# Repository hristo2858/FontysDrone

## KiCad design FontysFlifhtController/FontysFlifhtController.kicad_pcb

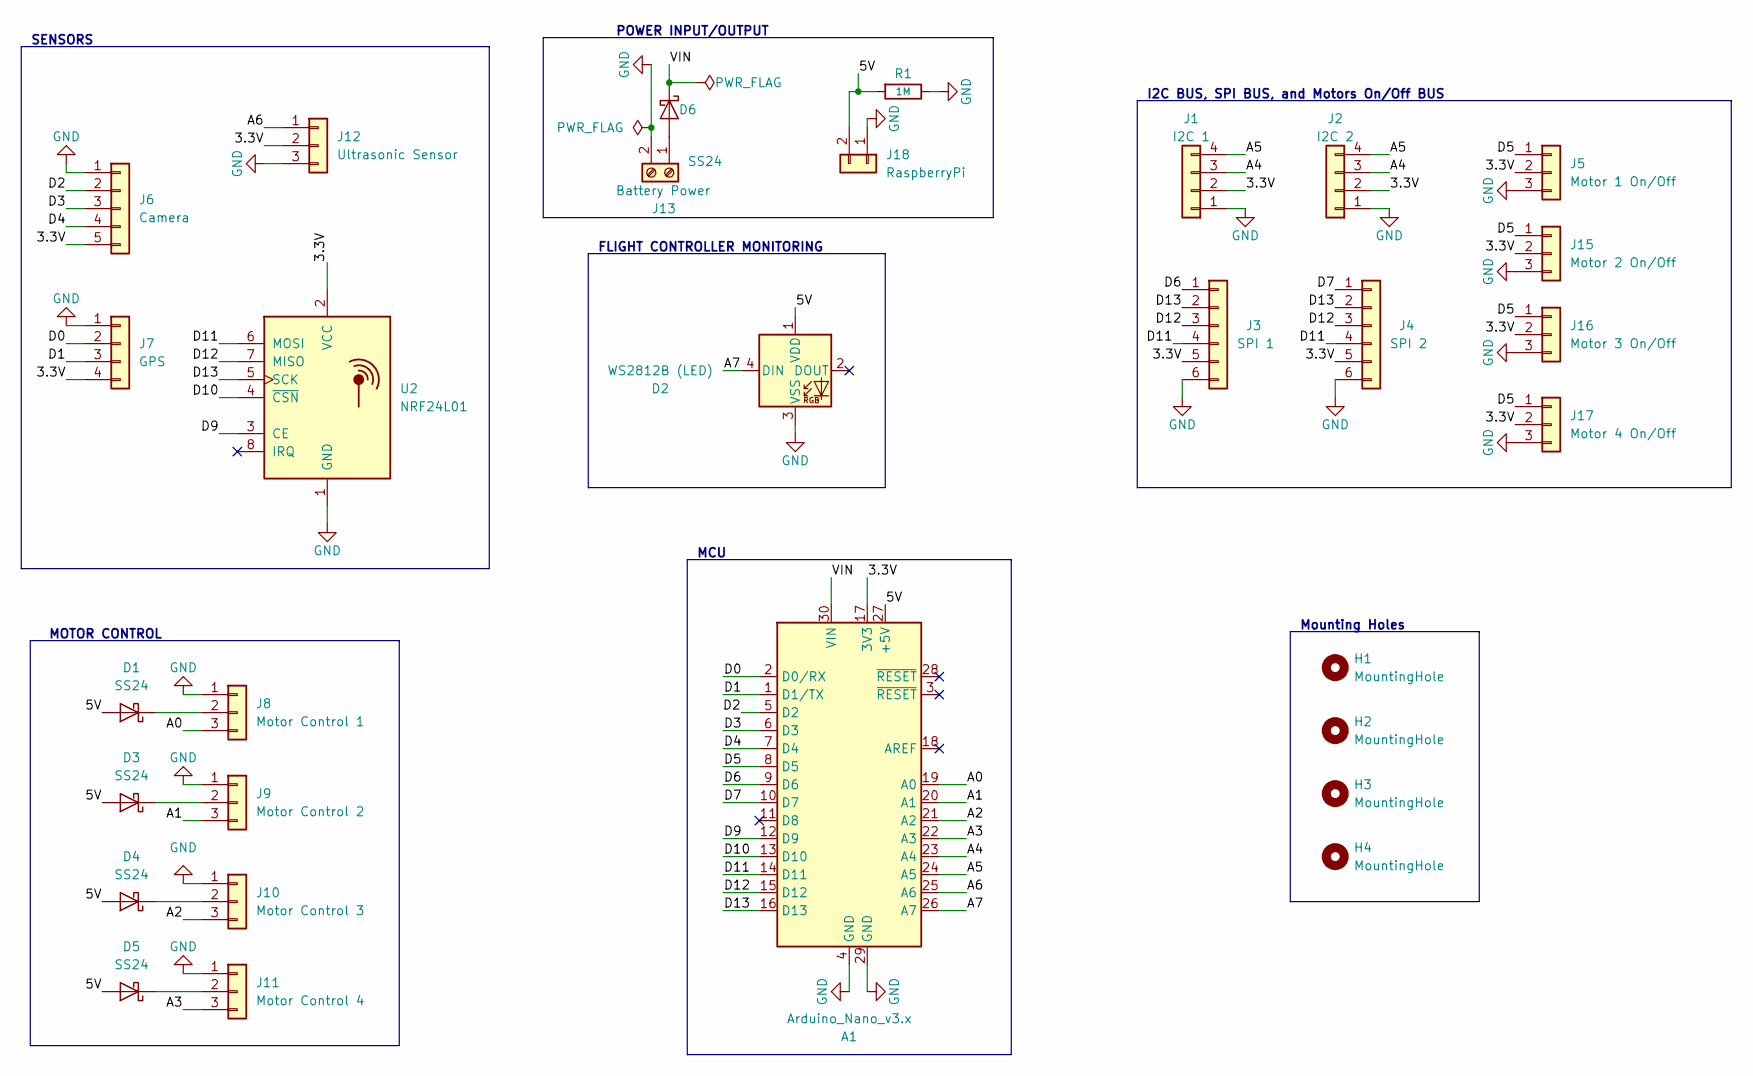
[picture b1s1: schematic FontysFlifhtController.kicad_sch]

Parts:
A1: Arduino_Nano_v3.x; Arduino_Nano
D1, D3, D4, D5, D6: SS24; D_SOD-123F; LCSC Part # C908678
D2: WS2812B (LED); LED_WS2812B_PLCC4_5.0x5.0mm_P3.2mm; LCSC Part # C2761795
H1, H2, H3, H4: MountingHole; MountingHole_2.7mm_M2.5
J1: I2C 1; JST_PH_S4B-PH-K_1x04_P2.00mm_Horizontal; LCSC Part # C157926
J2: I2C 2; JST_PH_S4B-PH-K_1x04_P2.00mm_Horizontal; LCSC Part # C157926
J3: SPI 1; JST_PH_S6B-PH-K_1x06_P2.00mm_Horizontal; LCSC Part # C157920
J4: SPI 2; JST_PH_S6B-PH-K_1x06_P2.00mm_Horizontal; LCSC Part # C157920
J5: Motor 1 On/Off; PinHeader_1x03_P2.54mm_Vertical; LCSC Part # C2932698
J6: Camera; JST_PH_S5B-PH-K_1x05_P2.00mm_Horizontal; LCSC Part # C157923
J7: GPS; PinHeader_1x04_P2.54mm_Vertical; LCSC Part # C2935975
J8: Motor Control 1; PinHeader_1x03_P2.54mm_Vertical; LCSC Part # C2932698
J9: Motor Control 2; PinHeader_1x03_P2.54mm_Vertical; LCSC Part # C2932698
J10: Motor Control 3; PinHeader_1x03_P2.54mm_Vertical; LCSC Part # C2932698
J11: Motor Control 4; PinHeader_1x03_P2.54mm_Vertical; LCSC Part # C2932698
J12: Ultrasonic Sensor; JST_PH_S3B-PH-K_1x03_P2.00mm_Horizontal; LCSC Part # C157929
J13: Battery Power; TerminalBlock_bornier-2_P5.08mm; LCSC Part # C474906
J15: Motor 2 On/Off; PinHeader_1x03_P2.54mm_Vertical; LCSC Part # C2932698
J16: Motor 3 On/Off; PinHeader_1x03_P2.54mm_Vertical; LCSC Part # C2932698
J17: Motor 4 On/Off; PinHeader_1x03_P2.54mm_Vertical; LCSC Part # C2932698
J18: RaspberryPi; PinHeader_1x02_P2.54mm_Vertical
R1: 1M; R_0805_2012Metric; LCSC Part # C17514
U2: NRF24L01; PinHeader_2x04_P2.54mm_Vertical; LCSC Part # C92271

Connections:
/3.3V: A1.17 (3V3), J1.2, J2.2, J3.5, J4.5, J5.2, J6.5, J7.4, J12.2, J15.2, J16.2, J17.2, U2.2 (VCC)
/5V: A1.27 (+5V), D1.2 (A), D2.1 (VDD), D3.2 (A), D4.2 (A), D5.2 (A), J18.2, R1.2
/A0: A1.19 (A0), J8.3
/A1: A1.20 (A1), J9.3
/A2: A1.21 (A2), J10.3
/A3: A1.22 (A3), J11.3
/A4: A1.23 (A4), J1.3, J2.3
/A5: A1.24 (A5), J1.4, J2.4
/A6: A1.25 (A6), J12.1
/A7: A1.26 (A7), D2.4 (DIN)
/D0: A1.2 (D0/RX), J7.2
/D1: A1.1 (D1/TX), J7.3
/D2: A1.5 (D2), J6.2
/D3: A1.6 (D3), J6.3
/D4: A1.7 (D4), J6.4
/D5: A1.8 (D5), J5.1, J15.1, J16.1, J17.1
/D6: A1.9 (D6), J3.1
/D7: A1.10 (D7), J4.1
/D9: A1.12 (D9), U2.3 (CE)
/D10: A1.13 (D10), U2.4 (~CSN)
/D11: A1.14 (D11), J3.4, J4.4, U2.6 (MOSI)
/D12: A1.15 (D12), J3.3, J4.3, U2.7 (MISO)
/D13: A1.16 (D13), J3.2, J4.2, U2.5 (SCK)
/VIN: A1.30 (VIN), D6.1 (K)
GND: A1.4 (GND), A1.29 (GND), D2.3 (VSS), J1.1, J2.1, J3.6, J4.6, J5.3, J6.1, J7.1, J8.1, J9.1, J10.1, J11.1, J12.3, J13.2, J15.3, J16.3, J17.3, J18.1, R1.1, U2.1 (GND)
unnamed: D1.1 (K), J8.2
unnamed: D3.1 (K), J9.2
unnamed: D4.1 (K), J10.2
unnamed: D5.1 (K), J11.2
unnamed: D6.2 (A), J13.1

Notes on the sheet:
FLIGHT CONTROLLER MONITORING
I2C BUS, SPI BUS, and Motors On/Off BUS
Mounting Holes
POWER INPUT/OUTPUT
MCU
SENSORS
MOTOR CONTROL

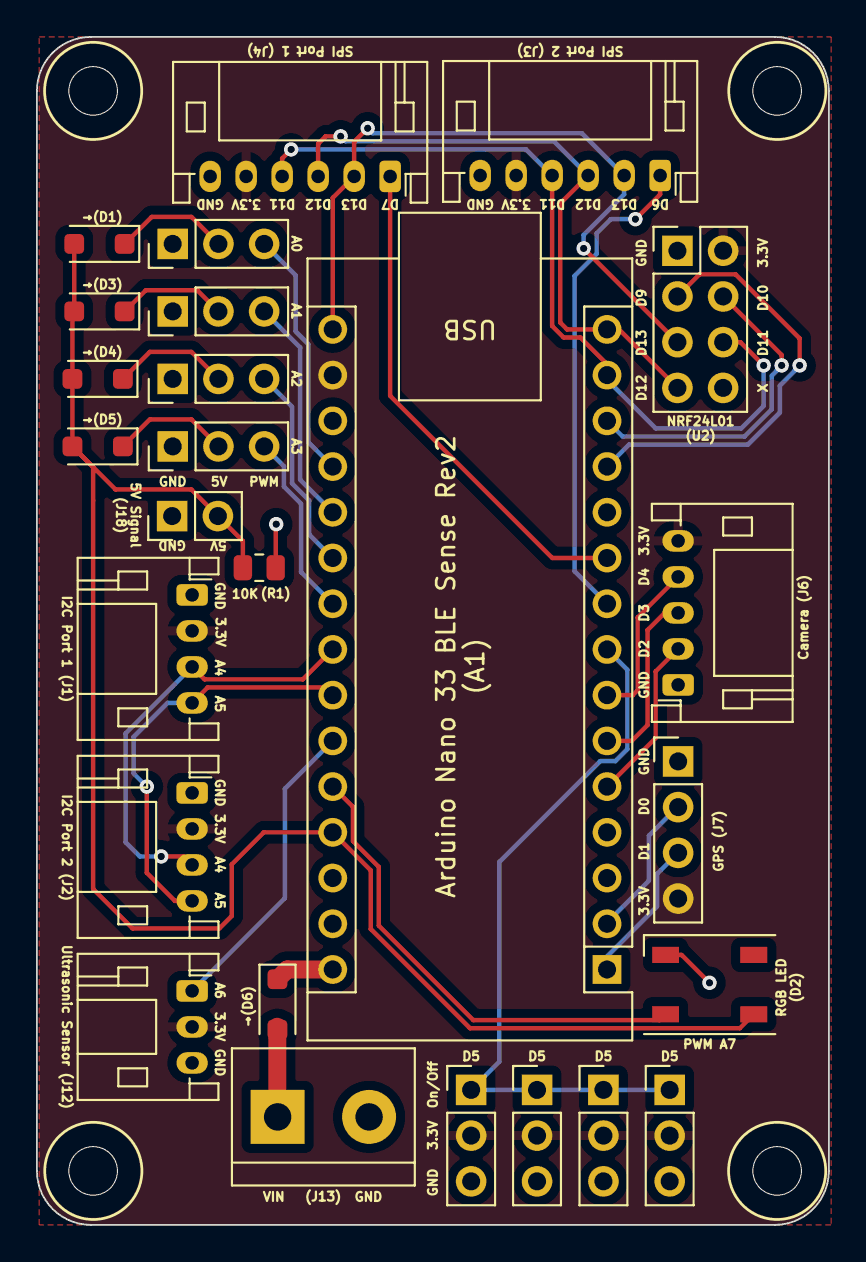
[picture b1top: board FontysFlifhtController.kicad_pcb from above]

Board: 2 copper layers, 44.0 x 66.0 mm, 30 parts (0 on the bottom side), 30 nets.

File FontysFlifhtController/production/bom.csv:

Designator,Footprint,Quantity,Value,LCSC Part #
A1,Arduino_Nano,1,Arduino_Nano_v3.x,C5371989 
"D1, D3, D4, D5",D_SOD-123F,4,SS24,C908678
D2,Arduino_Nano,1,Arduino_Nano_v3.x,C2761795
H1,MountingHole_2.7mm_M2.5,1,MountingHole,C5371989 
J1,JST_PH_S4B-PH-K_1x04_P2.00mm_Horizontal,1,I2C 1,C157926
J10,PinHeader_1x03_P2.54mm_Vertical,1,Motor Control 3,C2932698
J11,PinHeader_1x03_P2.54mm_Vertical,1,Motor Control 4,C2932698
J12,JST_PH_S3B-PH-K_1x03_P2.00mm_Horizontal,1,Ultrasonic Sensor,C157929
J13,TerminalBlock_bornier-2_P5.08mm,1,Battery Power,C474906
J14,PinHeader_1x01_P2.54mm_Vertical,1,RaspberryPi,C7501259
J15,PinHeader_1x03_P2.54mm_Vertical,1,Motor 2 On/Off,C2932698
J16,PinHeader_1x03_P2.54mm_Vertical,1,Motor 3 On/Off,C2932698
J17,PinHeader_1x03_P2.54mm_Vertical,1,Motor 4 On/Off,C2932698
J2,JST_PH_S4B-PH-K_1x04_P2.00mm_Horizontal,1,I2C 2,C157926
J3,JST_PH_S6B-PH-K_1x06_P2.00mm_Horizontal,1,SPI 1,C157920
J4,JST_PH_S6B-PH-K_1x06_P2.00mm_Horizontal,1,SPI 2,C157920
J5,PinHeader_1x03_P2.54mm_Vertical,1,Motor 1 On/Off,C2932698
J6,JST_PH_S5B-PH-K_1x05_P2.00mm_Horizontal,1,Camera,C157923
J7,PinHeader_1x04_P2.54mm_Vertical,1,GPS,C2935975
J8,PinHeader_1x03_P2.54mm_Vertical,1,Motor Control 1,C2932698
J9,PinHeader_1x03_P2.54mm_Vertical,1,Motor Control 2,C2932698
R1,805,1,1M,C17514
U2,PinHeader_2x04_P2.54mm_Vertical,1,NRF24L01,C92271

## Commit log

2023-03-20 project initialization
2023-03-22 Add IMU Hardware
2023-03-22 working IMU
2023-03-30 add drivers
2023-04-11 add pid
2023-04-11 add camera
2023-10-14 add the flight controller board
2024-03-21 Flight controller v2.0
2024-03-22 Add turn on/off functionality for the motors
2024-03-22 Improve board
2024-03-28 final changes
2024-04-13 edit labels
2024-04-13 add changes for feedback
2024-04-13 change resistor label
2024-05-06 something
2024-05-29 Add Camera Webserver
